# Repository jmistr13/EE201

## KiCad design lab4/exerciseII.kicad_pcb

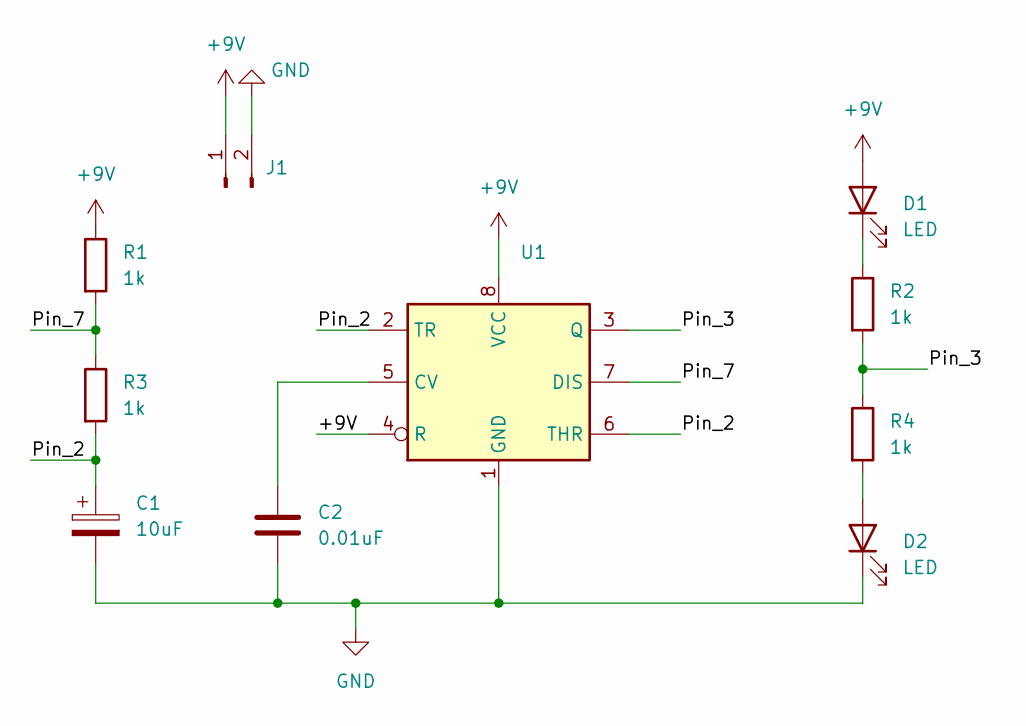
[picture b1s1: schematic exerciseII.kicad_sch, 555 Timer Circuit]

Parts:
C1: 10uF; CP_EIA-3216-18_Kemet-A_Pad1.58x1.35mm_HandSolder
C2: 0.01uF; C_0805_2012Metric_Pad1.18x1.45mm_HandSolder
D1, D2: LED; LED_1206_3216Metric_Pad1.42x1.75mm_HandSolder
J1: TerminalBlock_bornier-2_P5.08mm
R1, R2, R3, R4: 1k; R_0805_2012Metric_Pad1.20x1.40mm_HandSolder
U1: SOIC-8_3.9x4.9mm_P1.27mm

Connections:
+9V: D1.2 (A), J1.1, R1.1, U1.4 (R), U1.8 (VCC)
/Pin_2: C1.1, R3.2, U1.2 (TR), U1.6 (THR)
/Pin_3: R2.2, R4.1, U1.3 (Q)
/Pin_7: R1.2, R3.1, U1.7 (DIS)
GND: C1.2, C2.2, D2.1 (K), J1.2, U1.1 (GND)
unnamed: C2.1, U1.5 (CV)
unnamed: D1.1 (K), R2.1
unnamed: D2.2 (A), R4.2

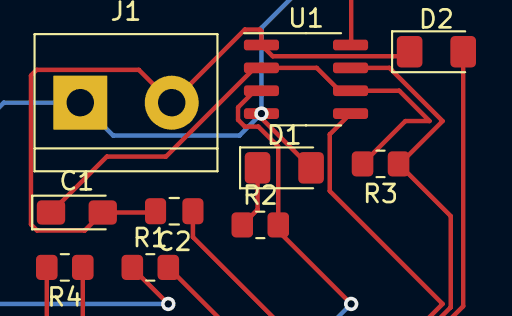
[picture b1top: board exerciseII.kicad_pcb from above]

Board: 2 copper layers, 10 parts (0 on the bottom side), 8 nets.

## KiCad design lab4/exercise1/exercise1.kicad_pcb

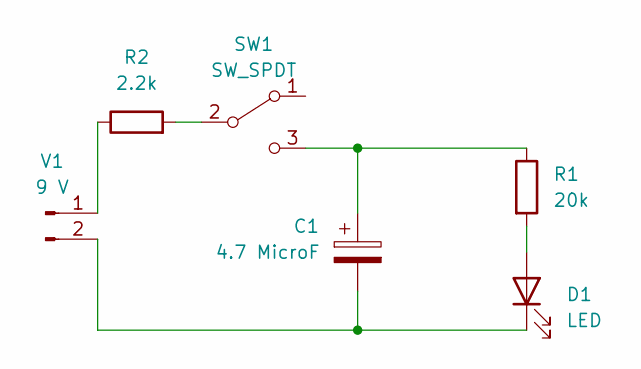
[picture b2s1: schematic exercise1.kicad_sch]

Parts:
C1: 4.7 MicroF; C_Radial_D5.0mm_H5.0mm_P2.00mm
D1: LED; LED_D5.0mm
R1: 20k; R_Axial_DIN0516_L15.5mm_D5.0mm_P20.32mm_Horizontal
R2: 2.2k; R_Axial_DIN0516_L15.5mm_D5.0mm_P20.32mm_Horizontal
SW1: SW_SPDT; SW_E-Switch_EG1224_SPDT_Angled
V1: 9 V; JST_PH_B2B-PH-K_1x02_P2.00mm_Vertical

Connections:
unnamed: C1.1, R1.1, SW1.3 (C)
unnamed: C1.2, D1.1 (K), V1.2
unnamed: D1.2 (A), R1.2
unnamed: R2.1, V1.1
unnamed: R2.2, SW1.2 (B)

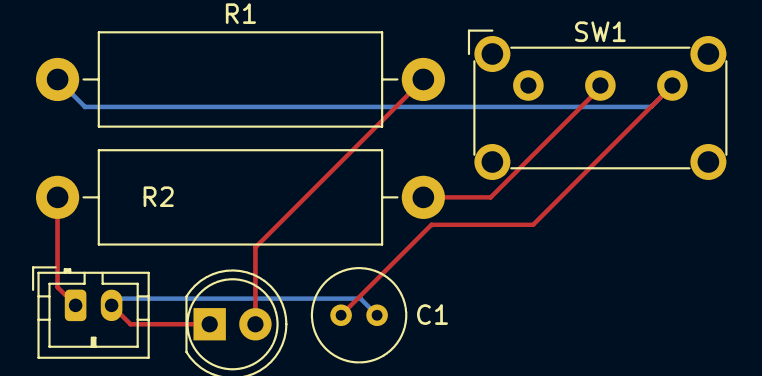
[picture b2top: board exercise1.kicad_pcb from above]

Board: 2 copper layers, 6 parts (0 on the bottom side), 5 nets.

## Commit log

2023-01-13 connected to github
2023-01-13 added aboutMe directory and new README file
2023-01-13 Updated README in aboutMe
2023-01-13 README edits
2023-01-13 reverted to creating aboutMe and readdded README
2023-01-13 edited README file
2023-01-13 editied readme again
2023-01-13 edited README
2023-01-13 fixed image in README
2023-01-21 uploaded exercise I-III files
2023-01-27 deleted arduino file :wq
2023-01-27 added arduino folder
2023-01-27 created lab4 branch, file; added exercise1 and II files
2023-01-27 Updated exerciseII file and added exercise2.txt(annotations)
2023-02-03 added files
2023-02-10 uploaded practice board photos
2023-02-17 finished PCB layouts
2023-02-17 added gerber files
